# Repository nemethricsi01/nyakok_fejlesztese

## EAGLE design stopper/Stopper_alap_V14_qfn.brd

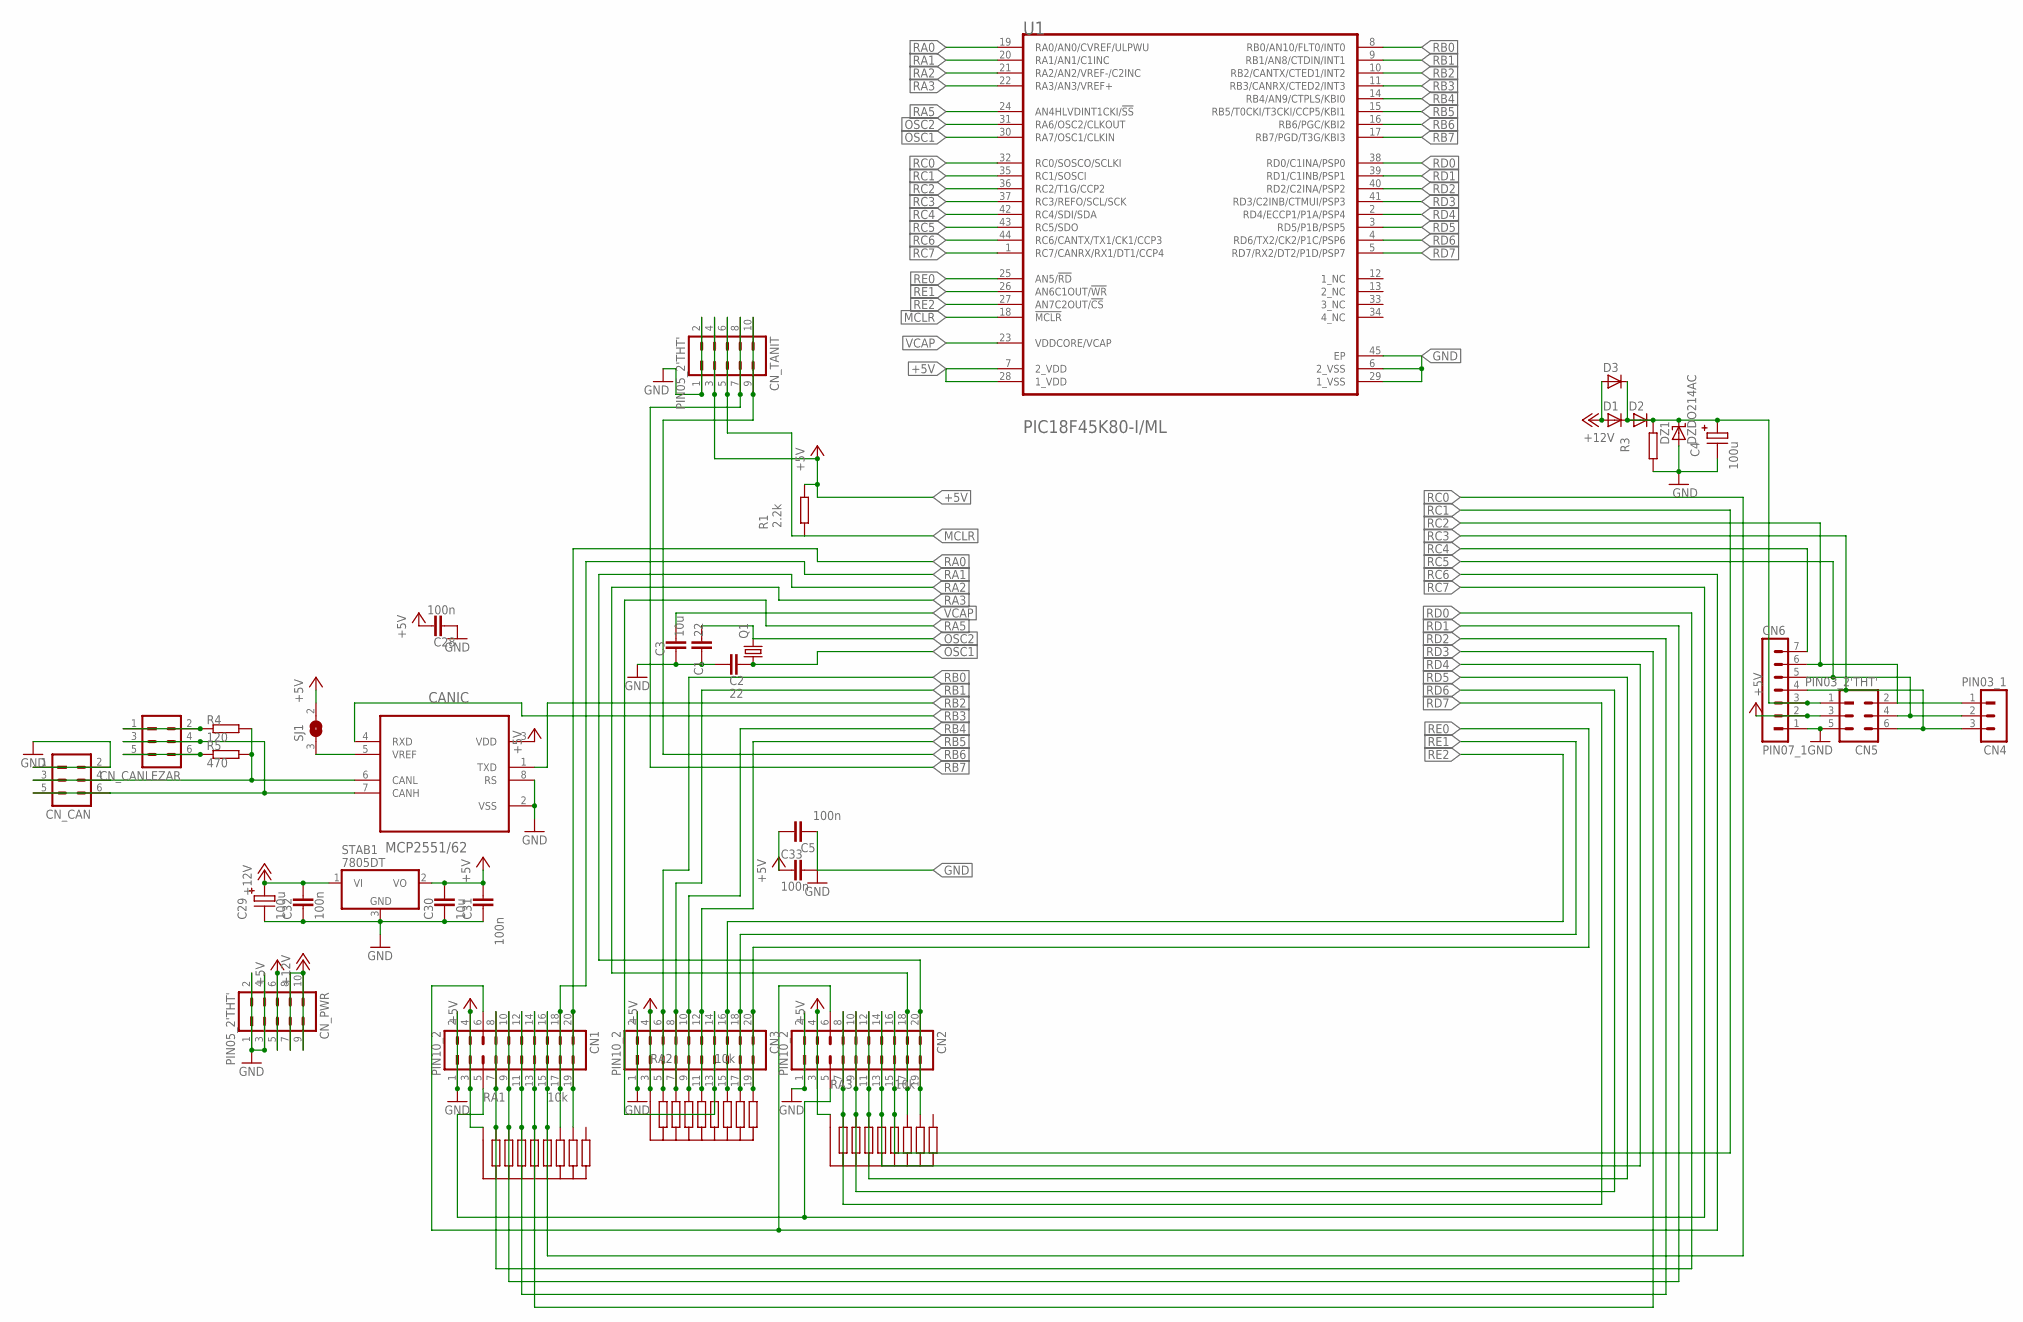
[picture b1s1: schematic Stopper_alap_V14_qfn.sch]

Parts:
C1, C2: 22; R0805
C3, C30: 10u; R0805
C4, C29: 100u; C_EL1RASZT07
C5, C28, C31, C32, C33: 100n; R0805
CANIC: MCP2551/62; DIP254P762X432-8
CN1, CN2, CN3: PIN10_2
CN4: PIN03_1
CN5: PIN03_2'THT'; PIN03_2
CN6: PIN07_1
CN_CAN: PIN03_2'THT'; PIN03_2
CN_CANLEZAR: PIN03_2'THT'; PIN03_2
CN_PWR: PIN05_2'THT'; PIN05_2
CN_TANIT: PIN05_2'THT'; PIN05_2
D1, D2: DDO214AC; DO214AC
D3: D1RNAGY; D1RASZTNAGY
DZ1: DZDO214AC; DO214AC
Q1: XTAL_2QS; XTAL_QS
R1: 2.2k; R0805@1
R3: R_EU0805; R0805@1
R4: 120; R0805@1
R5: 470; R0805@1
RA1, RA2, RA3: 10k; R_ARRAY
SJ1: SJ
STAB1: 7805DT; TO252
U1: MICROCHIP_PIC18F45K80-I-MLMICROCHIP_PIC18F45K80-I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; MICROCHIP_PIC18F45K80-I-ML_2

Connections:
+5V: C5.1, C28.1, C30.1, C31.1, C33.2, CANIC.3 (VDD), CN1.3, CN1.4, CN2.3, CN2.4, CN3.3, CN3.4, CN5.3, CN6.2, CN_PWR.5, CN_PWR.6, CN_TANIT.3, CN_TANIT.4, R1.2 (E), RA1.P$1 (A), RA2.P$1 (A), RA3.P$1 (A), SJ1.2, STAB1.2 (VO), U1.7 (2_VDD), U1.28 (1_VDD)
+12V: C29.P+, C32.1, CN_PWR.7, CN_PWR.8, CN_PWR.9, CN_PWR.10, D1.A, D3.P$1 (A), STAB1.1 (VI)
GND: C1.2, C2.2, C3.2, C4.P-, C5.2, C28.2, C29.P-, C30.2, C31.2, C32.2, C33.1, CANIC.2 (VSS), CANIC.8 (RS), CN1.1, CN1.2, CN2.1, CN2.2, CN3.1, CN3.2, CN5.5, CN6.1, CN_CAN.1, CN_CAN.2, CN_PWR.1, CN_PWR.2, CN_PWR.3, CN_PWR.4, CN_TANIT.1, CN_TANIT.2, DZ1.A, R3.1 (A), STAB1.3 (GND), U1.6 (2_VSS), U1.29 (1_VSS), U1.45 (EP)
MCLR: CN_TANIT.5, CN_TANIT.6, R1.1 (A), U1.18 (!MCLR!)
unnamed: CANIC.5 (VREF), SJ1.3 (1)
unnamed: C4.P+, CN5.1, CN6.3, D1.C, D2.A, D2.C, D3.P$2 (C), DZ1.C, R3.2 (E)
unnamed: CN_CANLEZAR.5, CN_CANLEZAR.6, R5.2 (E)
unnamed: CN_CANLEZAR.1, CN_CANLEZAR.2, R4.1 (A)
unnamed: CANIC.7 (CANH), CN_CAN.5, CN_CAN.6, CN_CANLEZAR.3, CN_CANLEZAR.4
unnamed: CANIC.6 (CANL), CN_CAN.3, CN_CAN.4, R4.2 (E), R5.1 (A)
OSC1: C2.1, Q1.1, U1.30 (RA7/OSC1/CLKIN)
OSC2: C1.1, Q1.2, U1.31 (RA6/OSC2/CLKOUT)
RA0: CN1.19, CN1.20, RA1.P$8 (E6), U1.19 (RA0/AN0/CVREF/ULPWU)
RA1: CN1.17, CN1.18, RA1.P$7 (E5), U1.20 (RA1/AN1/C1INC)
RA2: CN2.19, CN2.20, RA3.P$8 (E6), U1.21 (RA2/AN2/VREF-/C2INC)
RA3: CN2.17, CN2.18, RA3.P$7 (E5), U1.22 (RA3/AN3/VREF+)
RA5: CN3.13, CN3.14, RA2.P$6 (E4), U1.24 (AN4HLVDINT1CKI/!SS!)
RB0: CN3.5, CN3.6, RA2.P$2 (E), U1.8 (RB0/AN10/FLT0/INT0)
RB1: CN3.7, CN3.8, RA2.P$3 (E1), U1.9 (RB1/AN8/CTDIN/INT1)
RB2: CANIC.1 (TXD), U1.10 (RB2/CANTX/CTED1/INT2)
RB3: CANIC.4 (RXD), U1.11 (RB3/CANRX/CTED2/INT3)
RB4: CN3.9, CN3.10, RA2.P$4 (E2), U1.14 (RB4/AN9/CTPLS/KBI0)
RB5: CN3.11, CN3.12, RA2.P$5 (E3), U1.15 (RB5/T0CKI/T3CKI/CCP5/KBI1)
RB6: CN_TANIT.9, CN_TANIT.10, U1.16 (RB6/PGC/KBI2)
RB7: CN_TANIT.7, CN_TANIT.8, U1.17 (RB7/PGD/T3G/KBI3)
RC0: CN1.15, CN1.16, RA1.P$6 (E4), U1.32 (RC0/SOSCO/SCLKI)
RC1: CN2.15, CN2.16, RA3.P$6 (E4), U1.35 (RC1/SOSCI)
RC2: CN4.1, CN5.2, CN6.6, U1.36 (RC2/T1G/CCP2)
RC3: CN4.3, CN5.6, CN6.4, U1.37 (RC3/REFO/SCL/SCK)
RC4: CN6.7, U1.42 (RC4/SDI/SDA)
RC5: CN4.2, CN5.4, CN6.5, U1.43 (RC5/SDO)
RC6: CN1.6, CN2.6, U1.44 (RC6/CANTX/TX1/CK1/CCP3)
RC7: CN1.5, CN2.5, U1.1 (RC7/CANRX/RX1/DT1/CCP4)
RD0: CN1.7, CN1.8, RA1.P$2 (E), U1.38 (RD0/C1INA/PSP0)
RD1: CN1.9, CN1.10, RA1.P$3 (E1), U1.39 (RD1/C1INB/PSP1)
RD2: CN1.11, CN1.12, RA1.P$4 (E2), U1.40 (RD2/C2INA/PSP2)
RD3: CN1.13, CN1.14, RA1.P$5 (E3), U1.41 (RD3/C2INB/CTMUI/PSP3)
RD4: CN2.13, CN2.14, RA3.P$5 (E3), U1.2 (RD4/ECCP1/P1A/PSP4)
RD5: CN2.11, CN2.12, RA3.P$4 (E2), U1.3 (RD5/P1B/PSP5)
RD6: CN2.9, CN2.10, RA3.P$3 (E1), U1.4 (RD6/TX2/CK2/P1C/PSP6)
RD7: CN2.7, CN2.8, RA3.P$2 (E), U1.5 (RD7/RX2/DT2/P1D/PSP7)
RE0: CN3.19, CN3.20, RA2.P$9 (E7), U1.25 (AN5/!RD!)
RE1: CN3.17, CN3.18, RA2.P$8 (E6), U1.26 (AN6C1OUT/!WR!)
RE2: CN3.15, CN3.16, RA2.P$7 (E5), U1.27 (AN7C2OUT/!CS!)
VCAP: C3.1, U1.23 (VDDCORE/VCAP)

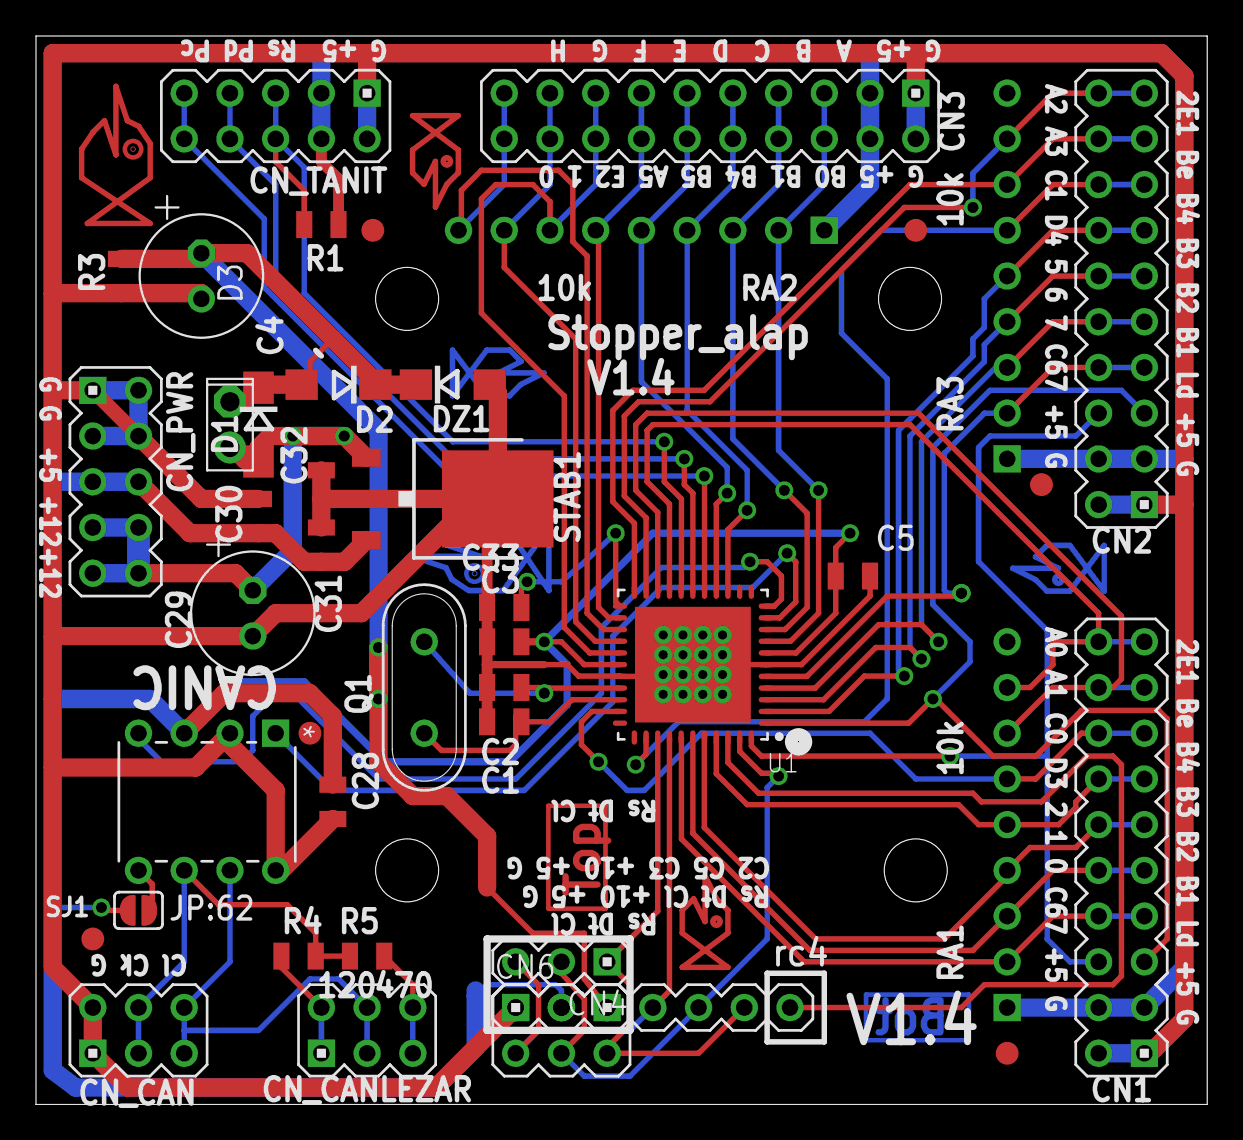
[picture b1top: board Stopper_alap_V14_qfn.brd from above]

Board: 2 copper layers, 65.1 x 59.4 mm, 37 parts (0 on the bottom side), 45 nets.

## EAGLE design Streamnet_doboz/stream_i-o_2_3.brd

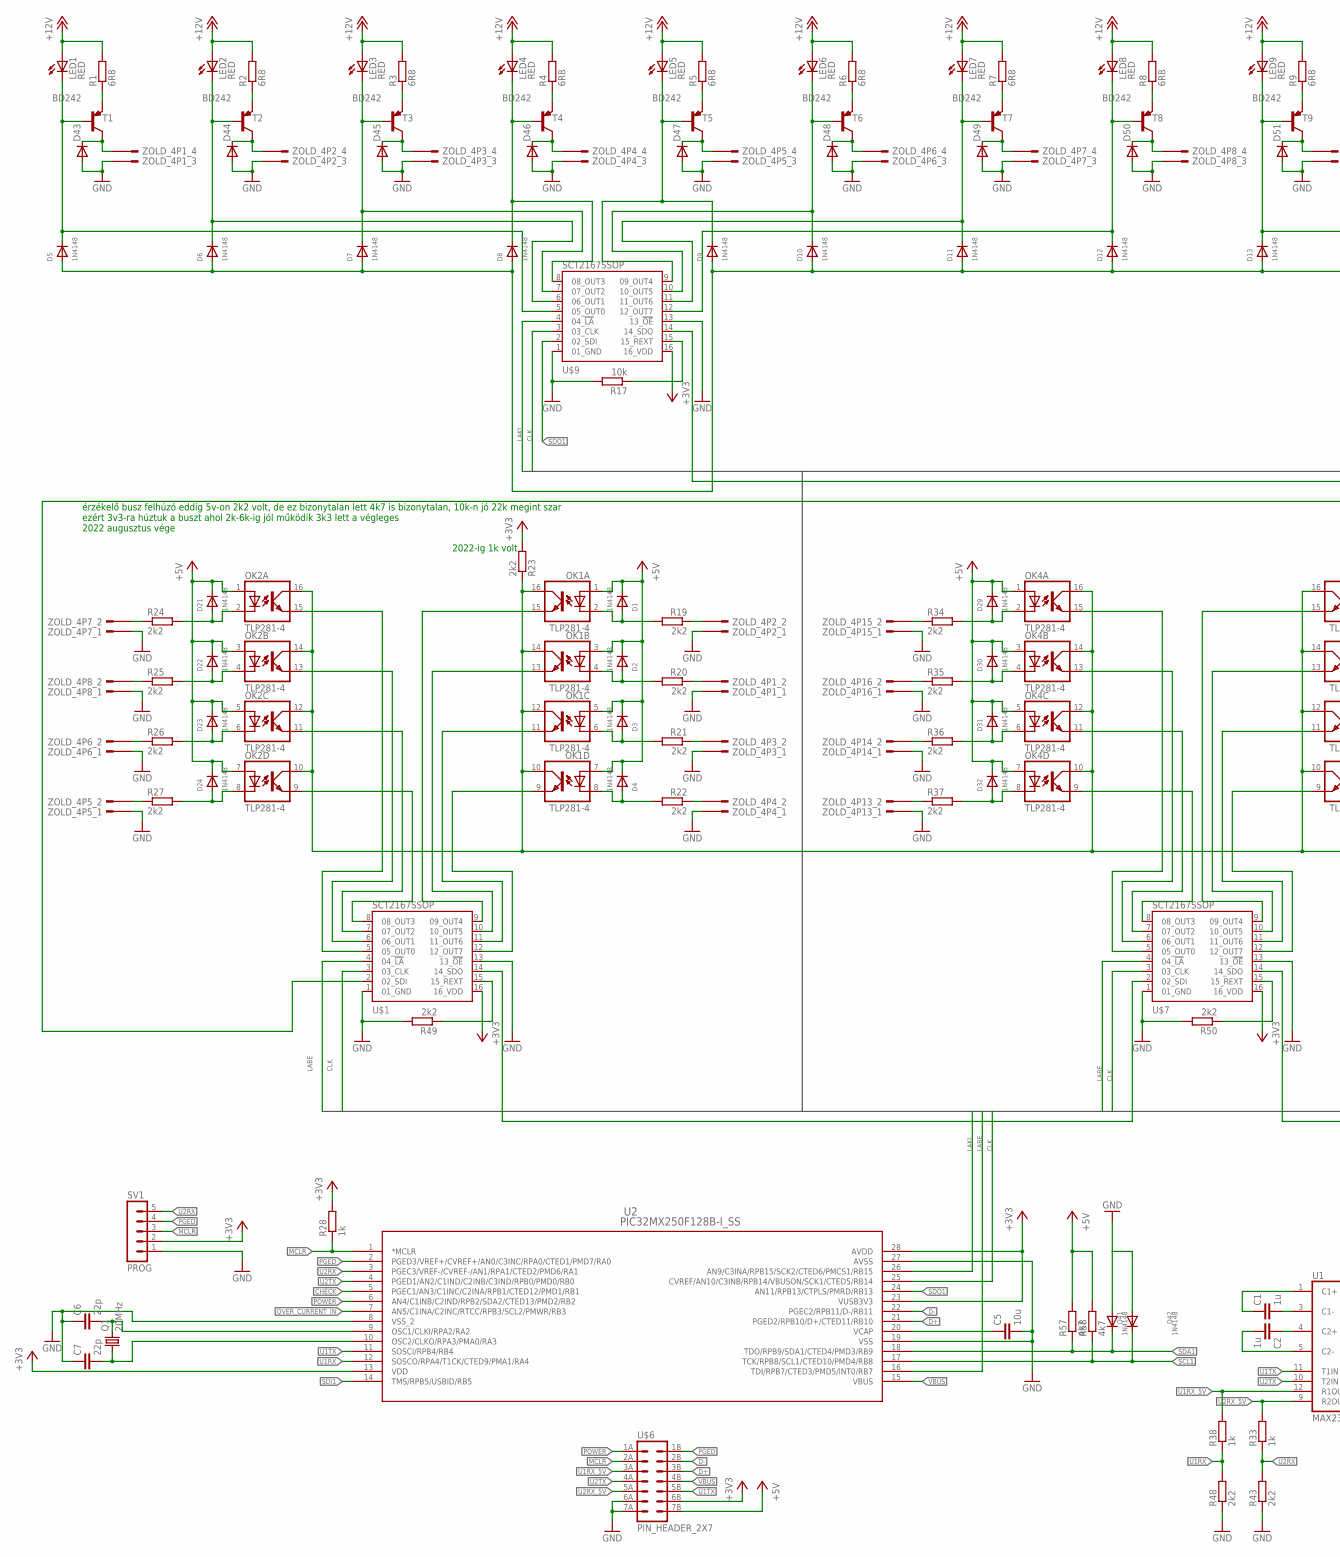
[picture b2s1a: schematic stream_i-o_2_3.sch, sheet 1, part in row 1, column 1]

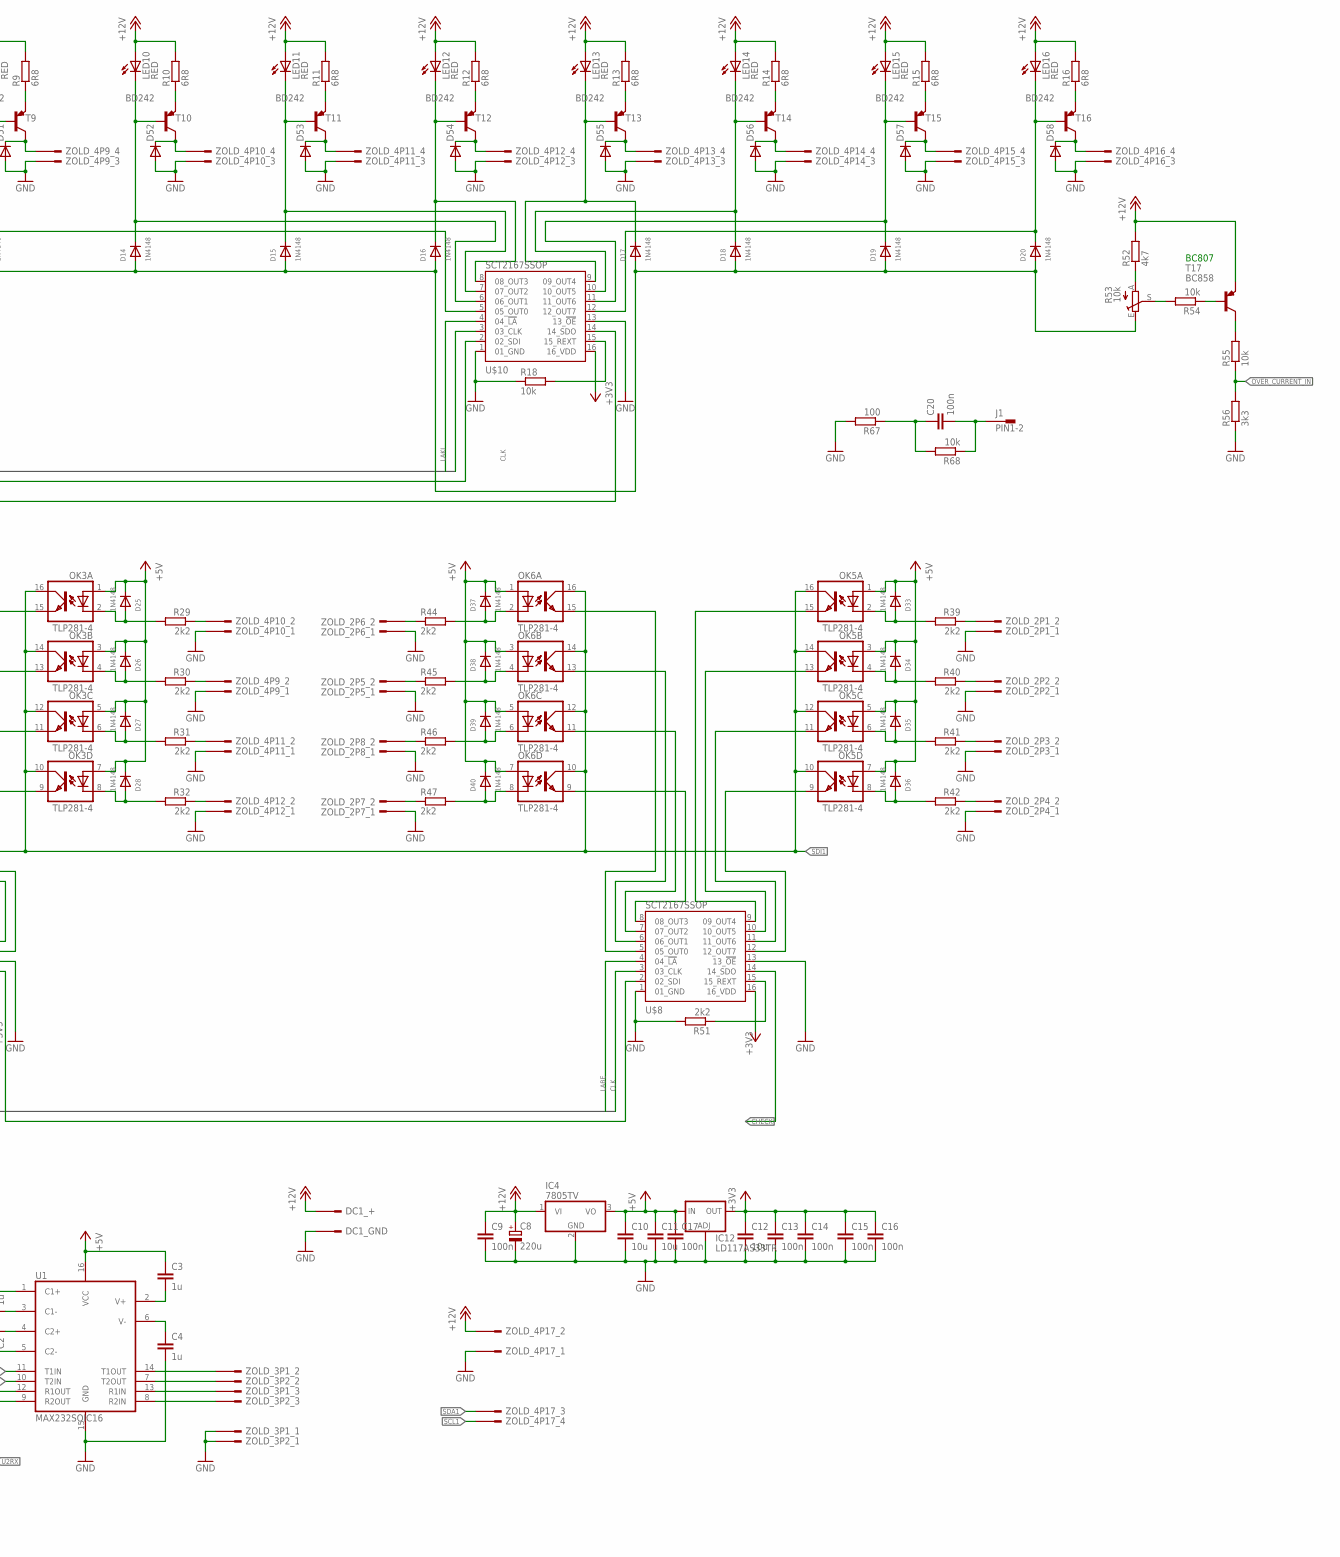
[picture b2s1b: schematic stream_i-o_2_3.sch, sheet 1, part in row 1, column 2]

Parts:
C1, C2, C3, C4: 1u; C0805
C5, C10, C11, C12: 10u; C0805
C6, C7: 22p; C0805
C8: 220u; E2,5-7
C9, C13, C14, C15, C16, C17, C20: 100n; C0805
D1, D2, D3, D4, D5, D6, D7, D8, D9, D10, D11, D12, D13, D14, D15, D16, D17, D18, D19, D20, D21, D22, D23, D24, D25, D26, D27, D28, D29, D30, D31, D32, D33, D34, D35, D36, D37, D38, D39, D40, D41, D42: 1N4148; SOD-323
D43, D44, D45, D46, D47, D48, D49, D50, D51, D52, D53, D54, D55, D56, D57, D58: DIODE-SOD-123; SOD-123
DC1: DC_55/21
IC4: 7805TV; TO220V
IC12: LD117AS33TR; SOT223
J1: PIN1-2; 62221
LED1, LED2, LED3, LED4, LED5, LED6, LED7, LED8, LED9, LED10, LED11, LED12, LED13, LED14, LED15, LED16: RED; CHIPLED_1206
OK1, OK2, OK3, OK4, OK5, OK6: TLP281-4; MINI-FLAT-16
Q1: 20MHz; HC49UP
R1, R2, R3, R4, R5, R6, R7, R8, R9, R10, R11, R12, R13, R14, R15, R16: 6R8; R0805
R17, R18, R54, R55, R68: 10k; R0805
R19, R20, R21, R22, R23, R24, R25, R26, R27, R29, R30, R31, R32, R34, R35, R36, R37, R39, R40, R41, R42, R43, R44, R45, R46, R47, R48, R49, R50, R51: 2k2; R0805
R28, R33, R38: 1k; R0805
R52, R57, R58: 4k7; R0805
R53: 10k; PT-6
R56: 3k3; R0805
R67: 100; R0805
SV1: PROG; MA05-1
T1, T2, T3, T4, T5, T6, T7, T8, T9, T10, T11, T12, T13, T14, T15, T16: BD242; TO220V
T17: BC858; SOT23-BEC
U1: MAX232SOIC16; SO016
U2: PIC32MX250F128B-I_SS; SSOP28_MC
U$1, U$7, U$8, U$9, U$10: SCT2167SSOP; SSOP
U$6: PIN_HEADER_2X7
ZOLD_2P1, ZOLD_2P2, ZOLD_2P3, ZOLD_2P4, ZOLD_2P5, ZOLD_2P6, ZOLD_2P7, ZOLD_2P8: ZOLD_KICSI_2P
ZOLD_3P1, ZOLD_3P2: ZOLD_KICSI_3P
ZOLD_4P1, ZOLD_4P2, ZOLD_4P3, ZOLD_4P4, ZOLD_4P5, ZOLD_4P6, ZOLD_4P7, ZOLD_4P8, ZOLD_4P9, ZOLD_4P10, ZOLD_4P11, ZOLD_4P12, ZOLD_4P13, ZOLD_4P14, ZOLD_4P15, ZOLD_4P16, ZOLD_4P17: ZOLD_KICSI_4P

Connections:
+3V3: C12.1, C13.1, C14.1, C15.1, C16.1, IC12.4 (OUT), R23.2, R28.2, SV1.2, U2.13 (VDD), U2.23 (VUSB3V3), U2.28 (AVDD), U$1.16 (16_VDD), U$6.6B (12), U$7.16 (16_VDD), U$8.16 (16_VDD), U$9.16 (16_VDD), U$10.16 (16_VDD)
+5V: C3.1, C10.1, C11.1, C17.1, D1.C, D2.C, D3.C, D4.C, D21.C, D22.C, D23.C, D24.C, D25.C, D26.C, D27.C, D28.C, D29.C, D30.C, D31.C, D32.C, D33.C, D34.C, D35.C, D36.C, D37.C, D38.C, D39.C, D40.C, IC4.3 (VO), IC12.3 (IN), OK1.1 (A), OK1.3 (A), OK1.5 (A), OK1.7 (A), OK2.1 (A), OK2.3 (A), OK2.5 (A), OK2.7 (A), OK3.1 (A), OK3.3 (A), OK3.5 (A), OK3.7 (A), OK4.1 (A), OK4.3 (A), OK4.5 (A), OK4.7 (A), OK5.1 (A), OK5.3 (A), OK5.5 (A), OK5.7 (A), OK6.1 (A), OK6.3 (A), OK6.5 (A), OK6.7 (A), R57.2, R58.2, U1.16 (VCC), U$6.7B (14)
+12V: C8.+, C9.1, DC1.2, IC4.1 (VI), LED1.A, LED2.A, LED3.A, LED4.A, LED5.A, LED6.A, LED7.A, LED8.A, LED9.A, LED10.A, LED11.A, LED12.A, LED13.A, LED14.A, LED15.A, LED16.A, R1.2, R2.2, R3.2, R4.2, R5.2, R6.2, R7.2, R8.2, R9.2, R10.2, R11.2, R12.2, R13.2, R14.2, R15.2, R16.2, R52.2, T17.E, ZOLD_4P17.2
CHECK: U2.5 (PGEC1/AN3/C1INC/C2INA/RPB1/CTED12/PMD1/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), U$8.14 (14_SDO)
CLK: U2.25 (CVREF/AN10/C3INB/RPB14/VBUSON/SCK1/CTED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), U$1.3 (03_CLK), U$7.3 (03_CLK), U$8.3 (03_CLK), U$9.3 (03_CLK), U$10.3 (03_CLK)
D+: U2.21 (PGED2/RPB10/D+/CTED11/RB10), U$6.3B (6)
D-: U2.22 (PGEC2/RPB11/D-/RB11), U$6.2B (4)
LABE: U2.16 (TDI/RPB7/CTED3/PMD5/INT0/RB7), U$1.4 (04_!LA!), U$7.4 (04_!LA!), U$8.4 (04_!LA!)
LAKI: U2.26 (AN9/C3INA/RPB15/SCK2/CTED6/PMCS1/RB15), U$9.4 (04_!LA!), U$10.4 (04_!LA!)
MCLR: R28.1, SV1.3, U2.1 (*MCLR), U$6.2A (3)
unnamed: D8.C, LED4.C, T4.1 (B), U$9.8 (08_OUT3)
unnamed: D5.C, LED1.C, T1.1 (B), U$9.5 (05_OUT0)
unnamed: R1.1, T1.3 (E)
unnamed: D43.C, T1.2 (C), ZOLD_4P1.4
unnamed: D6.C, LED2.C, T2.1 (B), U$9.6 (06_OUT1)
unnamed: R2.1, T2.3 (E)
unnamed: D44.C, T2.2 (C), ZOLD_4P2.4
unnamed: D7.C, LED3.C, T3.1 (B), U$9.7 (07_OUT2)
unnamed: R3.1, T3.3 (E)
unnamed: D45.C, T3.2 (C), ZOLD_4P3.4
unnamed: R4.1, T4.3 (E)
unnamed: D46.C, T4.2 (C), ZOLD_4P4.4
unnamed: D9.C, LED5.C, T5.1 (B), U$9.9 (09_OUT4)
unnamed: R5.1, T5.3 (E)
unnamed: D47.C, T5.2 (C), ZOLD_4P5.4
unnamed: D10.C, LED6.C, T6.1 (B), U$9.10 (10_OUT5)
unnamed: R6.1, T6.3 (E)
unnamed: D48.C, T6.2 (C), ZOLD_4P6.4
unnamed: D11.C, LED7.C, T7.1 (B), U$9.11 (11_OUT6)
unnamed: R7.1, T7.3 (E)
unnamed: D49.C, T7.2 (C), ZOLD_4P7.4
unnamed: D12.C, LED8.C, T8.1 (B), U$9.12 (12_OUT7)
unnamed: R8.1, T8.3 (E)
unnamed: D50.C, T8.2 (C), ZOLD_4P8.4
unnamed: R49.1, U$1.15 (15_REXT)
unnamed: C4.2, C5.2, C6.1, C7.1, C8.-, C9.2, C10.2, C11.2, C12.2, C13.2, C14.2, C15.2, C16.2, C17.2, D41.A, D42.A, D43.A, D44.A, D45.A, D46.A, D47.A, D48.A, D49.A, D50.A, D51.A, D52.A, D53.A, D54.A, D55.A, D56.A, D57.A, D58.A, DC1.1, IC4.2 (GND), IC12.1 (ADJ), R17.2, R18.1, R43.1, R48.1, R49.2, R50.2, R51.2, R56.1, R67.2, SV1.1, U1.15 (GND), U2.8 (VSS_2), U2.19 (VSS), U2.27 (AVSS), U$1.1 (01_GND), U$1.13 (13_!OE!), U$6.6A (11), U$6.7A (13), U$7.1 (01_GND), U$7.13 (13_!OE!), U$8.1 (01_GND), U$8.13 (13_!OE!), U$9.1 (01_GND), U$9.13 (13_!OE!), U$10.1 (01_GND), U$10.13 (13_!OE!), ZOLD_2P1.1, ZOLD_2P2.1, ZOLD_2P3.1, ZOLD_2P4.1, ZOLD_2P5.1, ZOLD_2P6.1, ZOLD_2P7.1, ZOLD_2P8.1, ZOLD_3P1.1, ZOLD_3P2.1, ZOLD_4P1.1, ZOLD_4P1.3, ZOLD_4P2.1, ZOLD_4P2.3, ZOLD_4P3.1, ZOLD_4P3.3, ZOLD_4P4.1, ZOLD_4P4.3, ZOLD_4P5.1, ZOLD_4P5.3, ZOLD_4P6.1, ZOLD_4P6.3, ZOLD_4P7.1, ZOLD_4P7.3, ZOLD_4P8.1, ZOLD_4P8.3, ZOLD_4P9.1, ZOLD_4P9.3, ZOLD_4P10.1, ZOLD_4P10.3, ZOLD_4P11.1, ZOLD_4P11.3, ZOLD_4P12.1, ZOLD_4P12.3, ZOLD_4P13.1, ZOLD_4P13.3, ZOLD_4P14.1, ZOLD_4P14.3, ZOLD_4P15.1, ZOLD_4P15.3, ZOLD_4P16.1, ZOLD_4P16.3, ZOLD_4P17.1
unnamed: U$9.14 (14_SDO), U$10.2 (02_SDI)
unnamed: R20.1, ZOLD_4P1.2
unnamed: D1.A, OK1.2 (C), R19.2
unnamed: R19.1, ZOLD_4P2.2
unnamed: D2.A, OK1.4 (C), R20.2
unnamed: R21.1, ZOLD_4P3.2
unnamed: D13.C, LED9.C, T9.1 (B), U$10.5 (05_OUT0)
unnamed: R9.1, T9.3 (E)
unnamed: D51.C, T9.2 (C), ZOLD_4P9.4
unnamed: D14.C, LED10.C, T10.1 (B), U$10.6 (06_OUT1)
unnamed: R10.1, T10.3 (E)
unnamed: D52.C, T10.2 (C), ZOLD_4P10.4
unnamed: D15.C, LED11.C, T11.1 (B), U$10.7 (07_OUT2)
unnamed: R11.1, T11.3 (E)
unnamed: D53.C, T11.2 (C), ZOLD_4P11.4
unnamed: D16.C, LED12.C, T12.1 (B), U$10.8 (08_OUT3)
unnamed: R12.1, T12.3 (E)
unnamed: D54.C, T12.2 (C), ZOLD_4P12.4
unnamed: D17.C, LED13.C, T13.1 (B), U$10.9 (09_OUT4)
unnamed: R13.1, T13.3 (E)
unnamed: D55.C, T13.2 (C), ZOLD_4P13.4
unnamed: D18.C, LED14.C, T14.1 (B), U$10.10 (10_OUT5)
unnamed: R14.1, T14.3 (E)
unnamed: D56.C, T14.2 (C), ZOLD_4P14.4
unnamed: D19.C, LED15.C, T15.1 (B), U$10.11 (11_OUT6)
unnamed: R15.1, T15.3 (E)
unnamed: D57.C, T15.2 (C), ZOLD_4P15.4
unnamed: D20.C, LED16.C, T16.1 (B), U$10.12 (12_OUT7)
unnamed: R16.1, T16.3 (E)
unnamed: D58.C, T16.2 (C), ZOLD_4P16.4
unnamed: D3.A, OK1.6 (C), R21.2
unnamed: R22.1, ZOLD_4P4.2
unnamed: D4.A, OK1.8 (C), R22.2
unnamed: R35.1, ZOLD_4P16.2
unnamed: D5.A, D6.A, D7.A, D8.A, D9.A, D10.A, D11.A, D12.A, D13.A, D14.A, D15.A, D16.A, D17.A, D18.A, D19.A, D20.A, R53.E
unnamed: D25.A, OK3.2 (C), R29.2
unnamed: D26.A, OK3.4 (C), R30.2
unnamed: OK1.15 (EMIT), U$1.9 (09_OUT4)
unnamed: OK1.13 (EMIT), U$1.10 (10_OUT5)
unnamed: OK1.11 (EMIT), U$1.11 (11_OUT6)
unnamed: OK1.9 (EMIT), U$1.12 (12_OUT7)
unnamed: D21.A, OK2.2 (C), R24.2
unnamed: D22.A, OK2.4 (C), R25.2
unnamed: D23.A, OK2.6 (C), R26.2
unnamed: D24.A, OK2.8 (C), R27.2
unnamed: R25.1, ZOLD_4P8.2
unnamed: R24.1, ZOLD_4P7.2
unnamed: R26.1, ZOLD_4P6.2
unnamed: R27.1, ZOLD_4P5.2
unnamed: OK5.15 (EMIT), U$8.9 (09_OUT4)
unnamed: OK2.15 (EMIT), U$1.5 (05_OUT0)
unnamed: OK2.13 (EMIT), U$1.6 (06_OUT1)
unnamed: OK2.11 (EMIT), U$1.7 (07_OUT2)
unnamed: OK2.9 (EMIT), U$1.8 (08_OUT3)
unnamed: D27.A, OK3.6 (C), R31.2
unnamed: D28.A, OK3.8 (C), R32.2
unnamed: R30.1, ZOLD_4P9.2
unnamed: R29.1, ZOLD_4P10.2
unnamed: R31.1, ZOLD_4P11.2
unnamed: R32.1, ZOLD_4P12.2
unnamed: R34.1, ZOLD_4P15.2
unnamed: OK3.15 (EMIT), U$7.9 (09_OUT4)
unnamed: OK3.13 (EMIT), U$7.10 (10_OUT5)
unnamed: OK3.11 (EMIT), U$7.11 (11_OUT6)
unnamed: OK3.9 (EMIT), U$7.12 (12_OUT7)
unnamed: D29.A, OK4.2 (C), R34.2
unnamed: D30.A, OK4.4 (C), R35.2
unnamed: D31.A, OK4.6 (C), R36.2
unnamed: D32.A, OK4.8 (C), R37.2
unnamed: OK5.13 (EMIT), U$8.10 (10_OUT5)
unnamed: OK4.13 (EMIT), U$7.6 (06_OUT1)
unnamed: R36.1, ZOLD_4P14.2
unnamed: R37.1, ZOLD_4P13.2
unnamed: OK5.11 (EMIT), U$8.11 (11_OUT6)
unnamed: OK4.15 (EMIT), U$7.5 (05_OUT0)
unnamed: R50.1, U$7.15 (15_REXT)
unnamed: OK4.11 (EMIT), U$7.7 (07_OUT2)
unnamed: OK4.9 (EMIT), U$7.8 (08_OUT3)
unnamed: D33.A, OK5.2 (C), R39.2
unnamed: D34.A, OK5.4 (C), R40.2
unnamed: D35.A, OK5.6 (C), R41.2
unnamed: D36.A, OK5.8 (C), R42.2
unnamed: R39.1, ZOLD_2P1.2
unnamed: R40.1, ZOLD_2P2.2
unnamed: R41.1, ZOLD_2P3.2
unnamed: R42.1, ZOLD_2P4.2
unnamed: OK5.9 (EMIT), U$8.12 (12_OUT7)
unnamed: R45.1, ZOLD_2P5.2
unnamed: R47.1, ZOLD_2P7.2
unnamed: R44.1, ZOLD_2P6.2
unnamed: R46.1, ZOLD_2P8.2
unnamed: D37.A, OK6.2 (C), R44.2
unnamed: D38.A, OK6.4 (C), R45.2
unnamed: D39.A, OK6.6 (C), R46.2
unnamed: D40.A, OK6.8 (C), R47.2
unnamed: C1.2, U1.3 (C1-)
unnamed: C1.1, U1.1 (C1+)
unnamed: C2.1, U1.4 (C2+)
unnamed: C2.2, U1.5 (C2-)
unnamed: C3.2, U1.2 (V+)
unnamed: OK6.15 (EMIT), U$8.5 (05_OUT0)
unnamed: OK6.13 (EMIT), U$8.6 (06_OUT1)
unnamed: OK6.11 (EMIT), U$8.7 (07_OUT2)
unnamed: OK6.9 (EMIT), U$8.8 (08_OUT3)
unnamed: R51.1, U$8.15 (15_REXT)
unnamed: U$1.2 (02_SDI), U$10.14 (14_SDO)
unnamed: U$1.14 (14_SDO), U$7.2 (02_SDI)
unnamed: U$7.14 (14_SDO), U$8.2 (02_SDI)
unnamed: U1.14 (T1OUT), ZOLD_3P1.2
unnamed: C4.1, U1.6 (V-)
unnamed: U1.13 (R1IN), ZOLD_3P1.3
unnamed: U1.7 (T2OUT), ZOLD_3P2.2
unnamed: U1.8 (R2IN), ZOLD_3P2.3
unnamed: C5.1, U2.20 (VCAP)
unnamed: C20.1, R67.1, R68.2
unnamed: R52.1, R53.A
unnamed: R53.S, R54.2
unnamed: R54.1, T17.B
unnamed: C20.2, J1.1, R68.1
unnamed: R55.2, T17.C
unnamed: C7.2, Q1.1, U2.10 (OSC2/CLKO/RPA3/PMA0/RA3)
unnamed: C6.2, Q1.2, U2.9 (OSC1/CLKI/RPA2/RA2)
unnamed: R17.1, U$9.15 (15_REXT)
unnamed: R18.2, U$10.15 (15_REXT)
OVER_CURRENT_IN: R55.1, R56.2, U2.7 (AN5/C1INA/C2INC/RTCC/RPB3/SCL2/PMWR/RB3)
PGED: SV1.4, U2.2 (PGED3/VREF+/CVREF+/AN0/C3INC/RPA0/CTED1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), U$6.1B (2)
POWER: U2.6 (AN4/C1INB/C2IND/RPB2/SDA2/CTED13/PMD2/R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), U$6.1A (1)
SCL1: D42.C, R58.1, U2.17 (TCK/RPB8/SCL1/CTED10/PMD4/RB8), ZOLD_4P17.4
SDA1: D41.C, R57.1, U2.18 (TDO/RPB9/SDA1/CTED4/PMD3/RB9), ZOLD_4P17.3
SDI1: OK1.10 (COL), OK1.12 (COL), OK1.14 (COL), OK1.16 (COL), OK2.10 (COL), OK2.12 (COL), OK2.14 (COL), OK2.16 (COL), OK3.10 (COL), OK3.12 (COL), OK3.14 (COL), OK3.16 (COL), OK4.10 (COL), OK4.12 (COL), OK4.14 (COL), OK4.16 (COL), OK5.10 (COL), OK5.12 (COL), OK5.14 (COL), OK5.16 (COL), OK6.10 (COL), OK6.12 (COL), OK6.14 (COL), OK6.16 (COL), R23.1, U2.14 (TMS/RPB5/USBID/RB5)
SDO1: U2.24 (AN11/RPB13/CTPLS/PMRD/RB13), U$9.2 (02_SDI)
U1RX: R38.1, R48.2, U2.12 (SOSCO/RPA4/T1CK/CTED9/PMA1/RA4)
U1RX_5V: R38.2, U1.12 (R1OUT), U$6.3A (5)
U1TX: U1.11 (T1IN), U2.11 (SOSCI/RPB4/RB4), U$6.5B (10)
U2RX: R33.1, R43.2, SV1.5, U2.3 (PGEC3/VREF-/CVREF-/AN1/RPA1/CTED2/PMD6/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)
U2RX_5V: R33.2, U1.9 (R2OUT), U$6.5A (9)
U2TX: U1.10 (T2IN), U2.4 (PGED1/AN2/C1IND/C2INB/C3IND/RPB0/PMD0/R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), U$6.4A (7)
VBUS: U2.15 (VBUS), U$6.4B (8)

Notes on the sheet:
2022-ig 1k volt
érzékelő busz felhúzó eddig 5v-on 2k2 volt, de ez bizonytalan lett 4k7 is bizonytalan, 10k-n jó 22k megint szar ezért 3v3-ra húztuk a buszt ahol 2k-6k-ig jól működik 3k3 lett a végleges 2022 augusztus vége
BC807

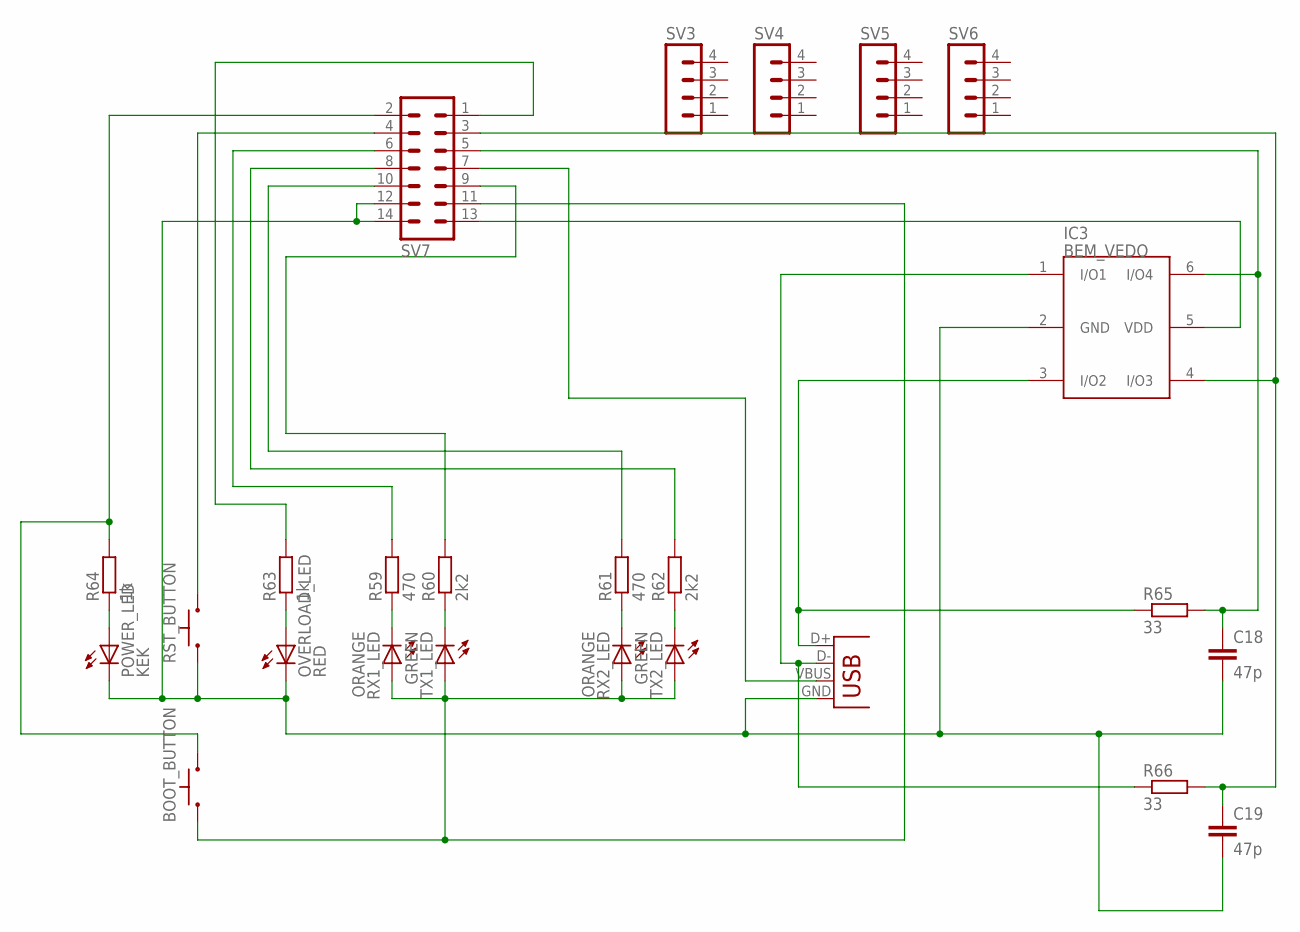
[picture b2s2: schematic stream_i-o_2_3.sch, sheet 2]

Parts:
BOOT_BUTTON: BUTTONRACON12; RACON12
C18, C19: 47p; C0805
IC3: BEM_VEDO; TSOP-6
JP1: USBPTH-VERTICAL; USB-B-PTH-VERTICAL
OVERLOAD_LED: RED; LED5MM
POWER_LED: KEK; LED5MM
R59, R61: 470; R0805
R60, R62: 2k2; R0805
R63, R64: 1k; R0805
R65, R66: 33; R0805
RST_BUTTON: BUTTONRACON12; RACON12
RX1_LED, RX2_LED: ORANGE; LED5MM
SV3, SV4, SV5, SV6: MA04-1
SV7: MA07-2
TX1_LED, TX2_LED: GREEN; LED5MM

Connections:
unnamed: R59.1, RX1_LED.K (C)
unnamed: R60.1, TX1_LED.K (C)
unnamed: R61.1, RX2_LED.K (C)
unnamed: IC3.5 (VDD), SV7.13
unnamed: R62.1, TX2_LED.K (C)
unnamed: RST_BUTTON.3 (S), RST_BUTTON.4 (S), SV7.4
unnamed: R59.2, SV7.6
unnamed: R60.2, SV7.9
unnamed: R61.2, SV7.10
unnamed: R62.2, SV7.8
unnamed: C18.2, C19.2, IC3.2 (GND), JP1.GND, OVERLOAD_LED.K (C), POWER_LED.K (C), RST_BUTTON.1, RST_BUTTON.2, SV7.12, SV7.14
unnamed: POWER_LED.A, R64.1
unnamed: OVERLOAD_LED.A, R63.1
unnamed: IC3.3 (I/O2), JP1.D+, R65.1
unnamed: BOOT_BUTTON.3 (S), BOOT_BUTTON.4 (S), R64.2, SV7.2
unnamed: R63.2, SV7.1
unnamed: C18.1, IC3.6 (I/O4), R65.2, SV7.5
unnamed: JP1.VBUS, SV7.7
unnamed: C19.1, IC3.4 (I/O3), R66.2, SV7.3
unnamed: IC3.1 (I/O1), JP1.D-, R66.1
unnamed: BOOT_BUTTON.1, BOOT_BUTTON.2, RX1_LED.A, RX2_LED.A, SV7.11, TX1_LED.A, TX2_LED.A

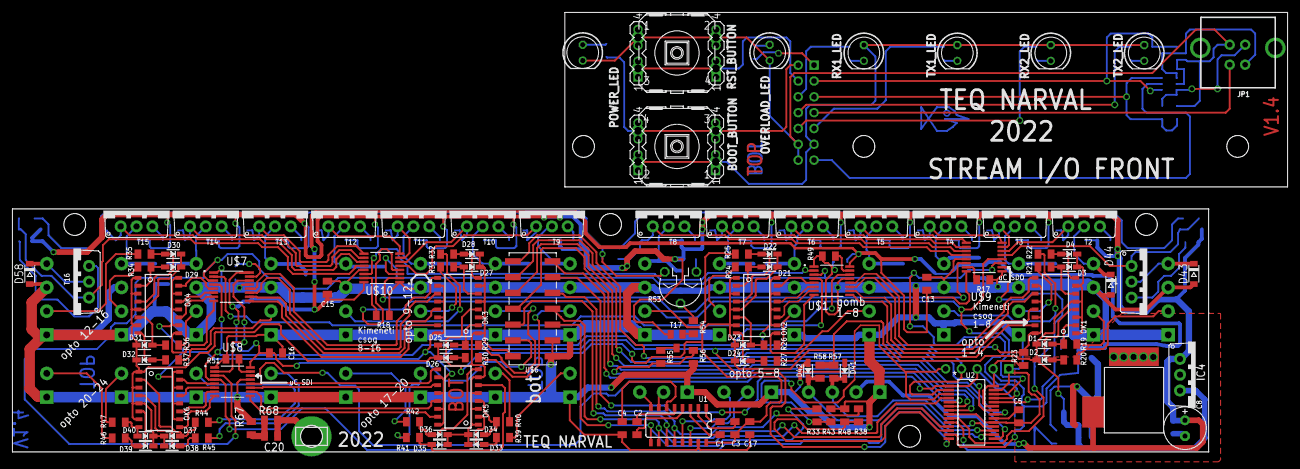
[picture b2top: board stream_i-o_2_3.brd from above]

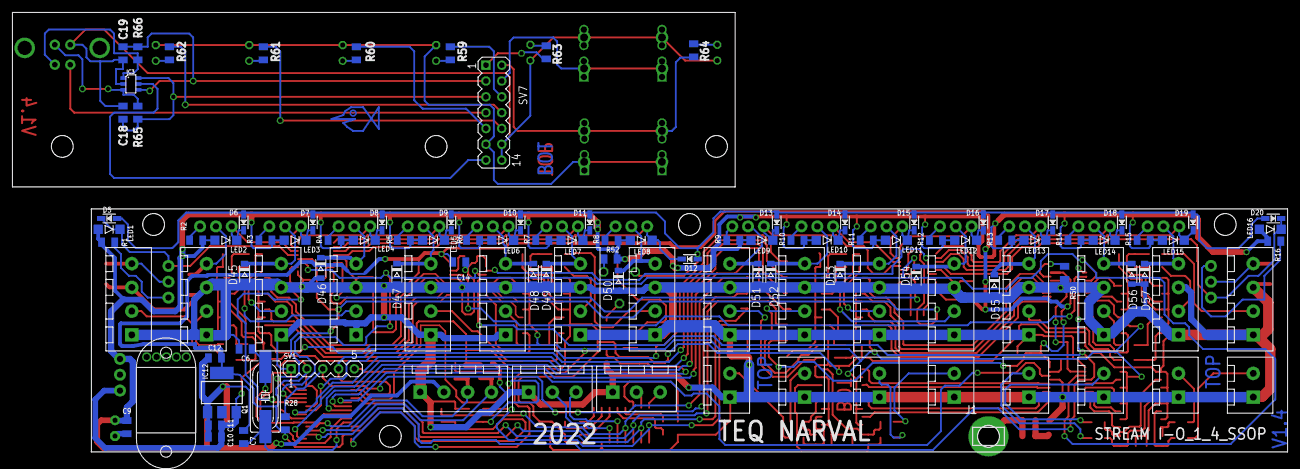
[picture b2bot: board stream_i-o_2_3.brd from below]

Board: 2 copper layers, 192.0 x 39.0 mm, 241 parts (115 on the bottom side), 195 nets.

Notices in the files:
parts and their libraries:
microbuilder: This work is placed in the public domain, and may be freely used for commercial and non-commercial work with the following conditions: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
SparkFun-DigitalIC: Licensing: Creative Commons ShareAlike 4.0 International - https://creativecommons.org/licenses/by-sa/4.0
